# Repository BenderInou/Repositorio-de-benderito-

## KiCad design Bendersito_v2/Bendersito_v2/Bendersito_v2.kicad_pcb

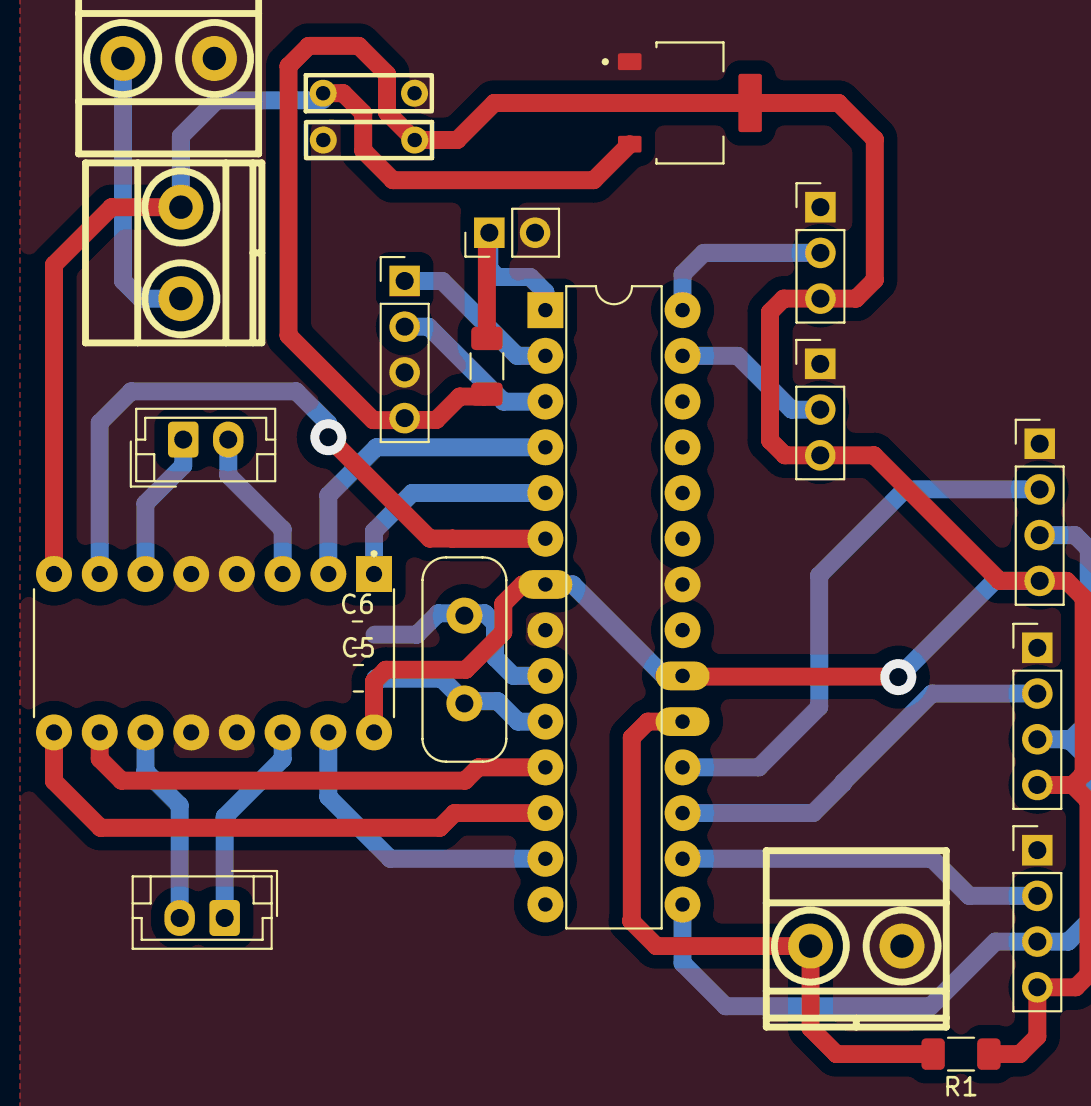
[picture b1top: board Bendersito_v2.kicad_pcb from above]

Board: 2 copper layers, 22 parts (0 on the bottom side), 26 nets.

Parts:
BAT1: BORNERA2
Bluetooth1: PinHeader_1x04_P2.54mm_Vertical
C1, C2: C; CAP_0.2
C5, C6: C; C_0805_2012Metric
CNY70_1, CNY70_2: PinHeader_1x03_P2.54mm_Vertical
J1: MOTOR DE; JST_EH_B2B-EH-A_1x02_P2.50mm_Vertical
J2: MOTOR IZ; JST_EH_B2B-EH-A_1x02_P2.50mm_Vertical
J4: Conn_02x01; PinHeader_1x02_P2.54mm_Vertical
PULSADOR1: BORNERA2
R1: R; R_1206_3216Metric_Pad1.30x1.75mm_HandSolder
R2: 10k; R_1206_3216Metric_Pad1.30x1.75mm_HandSolder
SENSOR_1, SENSOR_2, SENSOR_3: PinHeader_1x04_P2.54mm_Vertical
SWICH1: BORNERA2
U1: ATmega328P-P; DIP-28_W7.62mm
U2: L293; DIP880W50P254L2000H510Q16
U3: 5V; SOT229P700X180-4N
Y1: ECS-160-S-4X; XTAL_ECS-160-S-4X

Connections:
5V: Bluetooth1.4, C2.1, CNY70_1.3, CNY70_2.3, R1.1, R2.2, SENSOR_1.4, SENSOR_2.4, SENSOR_3.4, U1.7 (VCC), U1.20 (AVCC), U2.16 (VCC1), U3.2 (VOUT), U3.4 (VOUT)
DATO_PULS: PULSADOR1.1, R1.2, U1.19 (PB5)
ECHO1: SENSOR_1.2, U1.16 (PB2)
ECHO2: SENSOR_2.2, U1.17 (PB3)
ECHO3: SENSOR_3.2, U1.18 (PB4)
EN1: U1.4 (PD2), U2.2 (1A)
EN2: U1.6 (PD4), U2.7 (2A)
EN3: U1.11 (PD5), U2.10 (3A)
EN4: U1.13 (PD7), U2.15 (4A)
ENA: U1.5 (PD3), U2.1 (EN1,2)
ENB: U1.12 (PD6), U2.9 (EN3,4)
GND: BAT1.1, Bluetooth1.3, C1.2, C2.2, C5.1, C6.1, CNY70_1.1, CNY70_2.1, J4.2, PULSADOR1.2, SENSOR_1.1, SENSOR_2.1, SENSOR_3.1, U1.8 (GND), U1.22 (GND), U2.4 (GND), U2.5 (GND), U2.12 (GND), U2.13 (GND), U3.1 (ADJ/GND)
unnamed: BAT1.2, SWICH1.1
unnamed: J1.2, U2.11 (3A)
unnamed: J2.2, U2.3 (1Y)
unnamed: J2.1, U2.6 (2Y)
unnamed: J1.1, U2.14 (4Y)
PB6: C6.2, U1.9 (XTAL1/PB6), Y1.2
PB7: C5.2, U1.10 (XTAL2/PB7), Y1.1
PIN_ANALOG_1: CNY70_1.2, U1.28 (PC5)
PIN_ANALOG_2: CNY70_2.2, U1.27 (PC4)
RESET: J4.1, R2.1, U1.1 (~RESET/PC6)
RX0: Bluetooth1.1, U1.2 (PD0)
TIGGER: SENSOR_1.3, SENSOR_2.3, SENSOR_3.3, U1.15 (PB1)
TX1: Bluetooth1.2, U1.3 (PD1)
VCC: C1.1, SWICH1.2, U2.8 (VCC2), U3.3 (VIN)

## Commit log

2023-12-07 prueba
